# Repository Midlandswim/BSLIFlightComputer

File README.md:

BSLI Vanilla Board 

DevBoard for BSLI Liquid Rocket Systems Flight Computer

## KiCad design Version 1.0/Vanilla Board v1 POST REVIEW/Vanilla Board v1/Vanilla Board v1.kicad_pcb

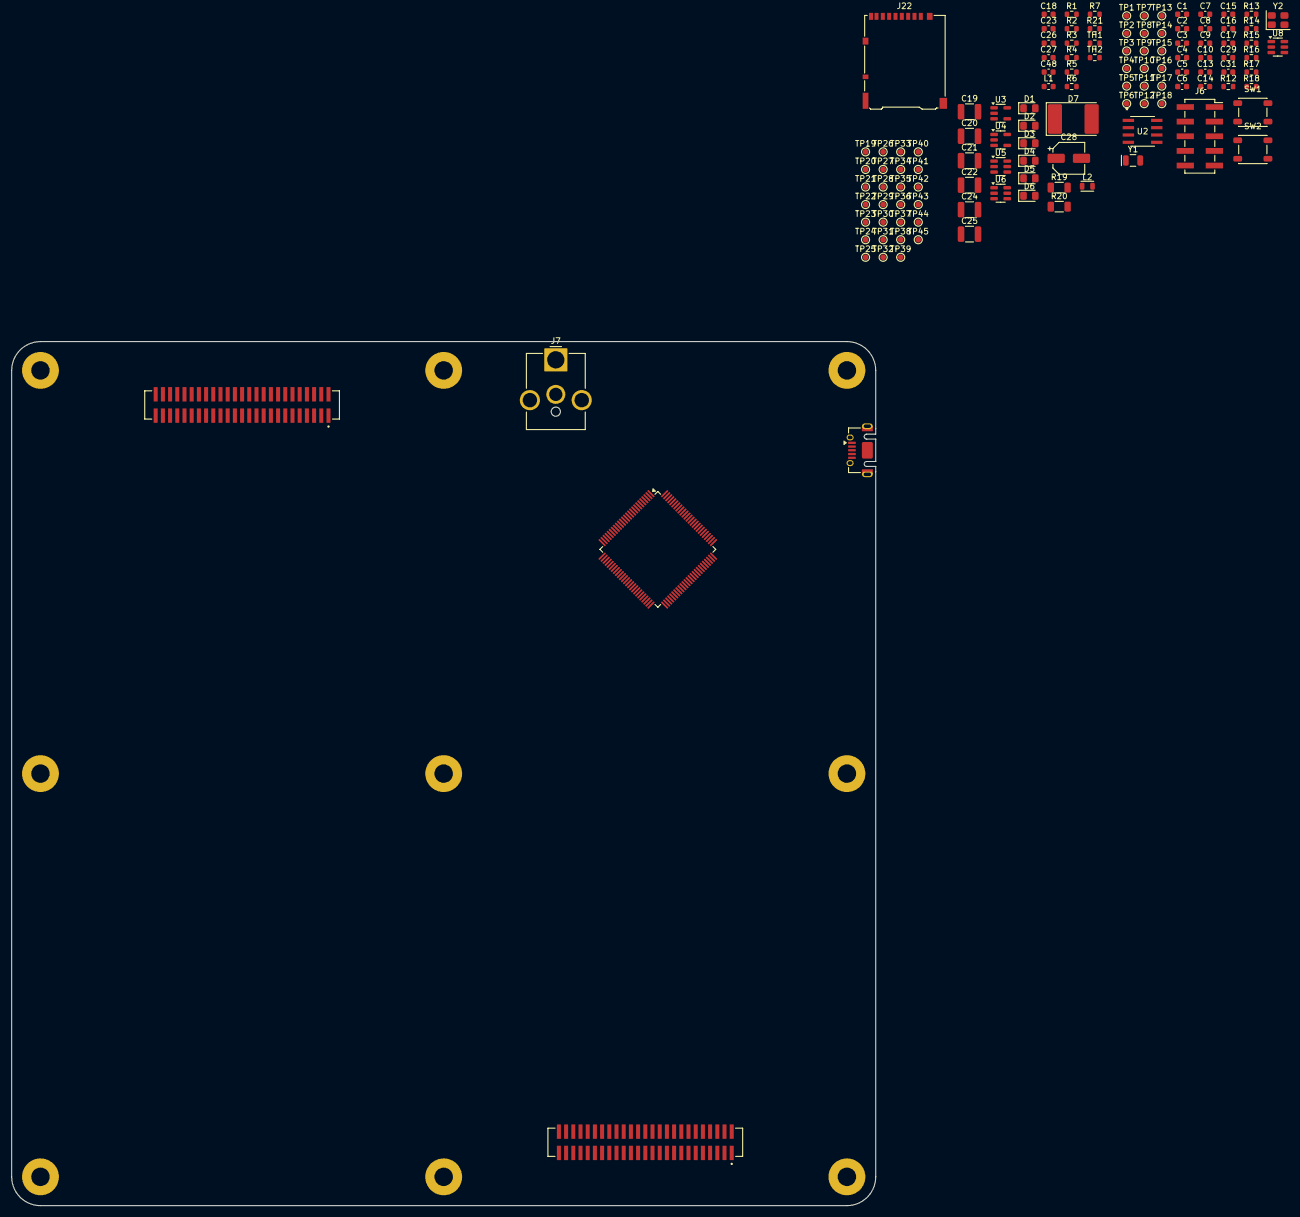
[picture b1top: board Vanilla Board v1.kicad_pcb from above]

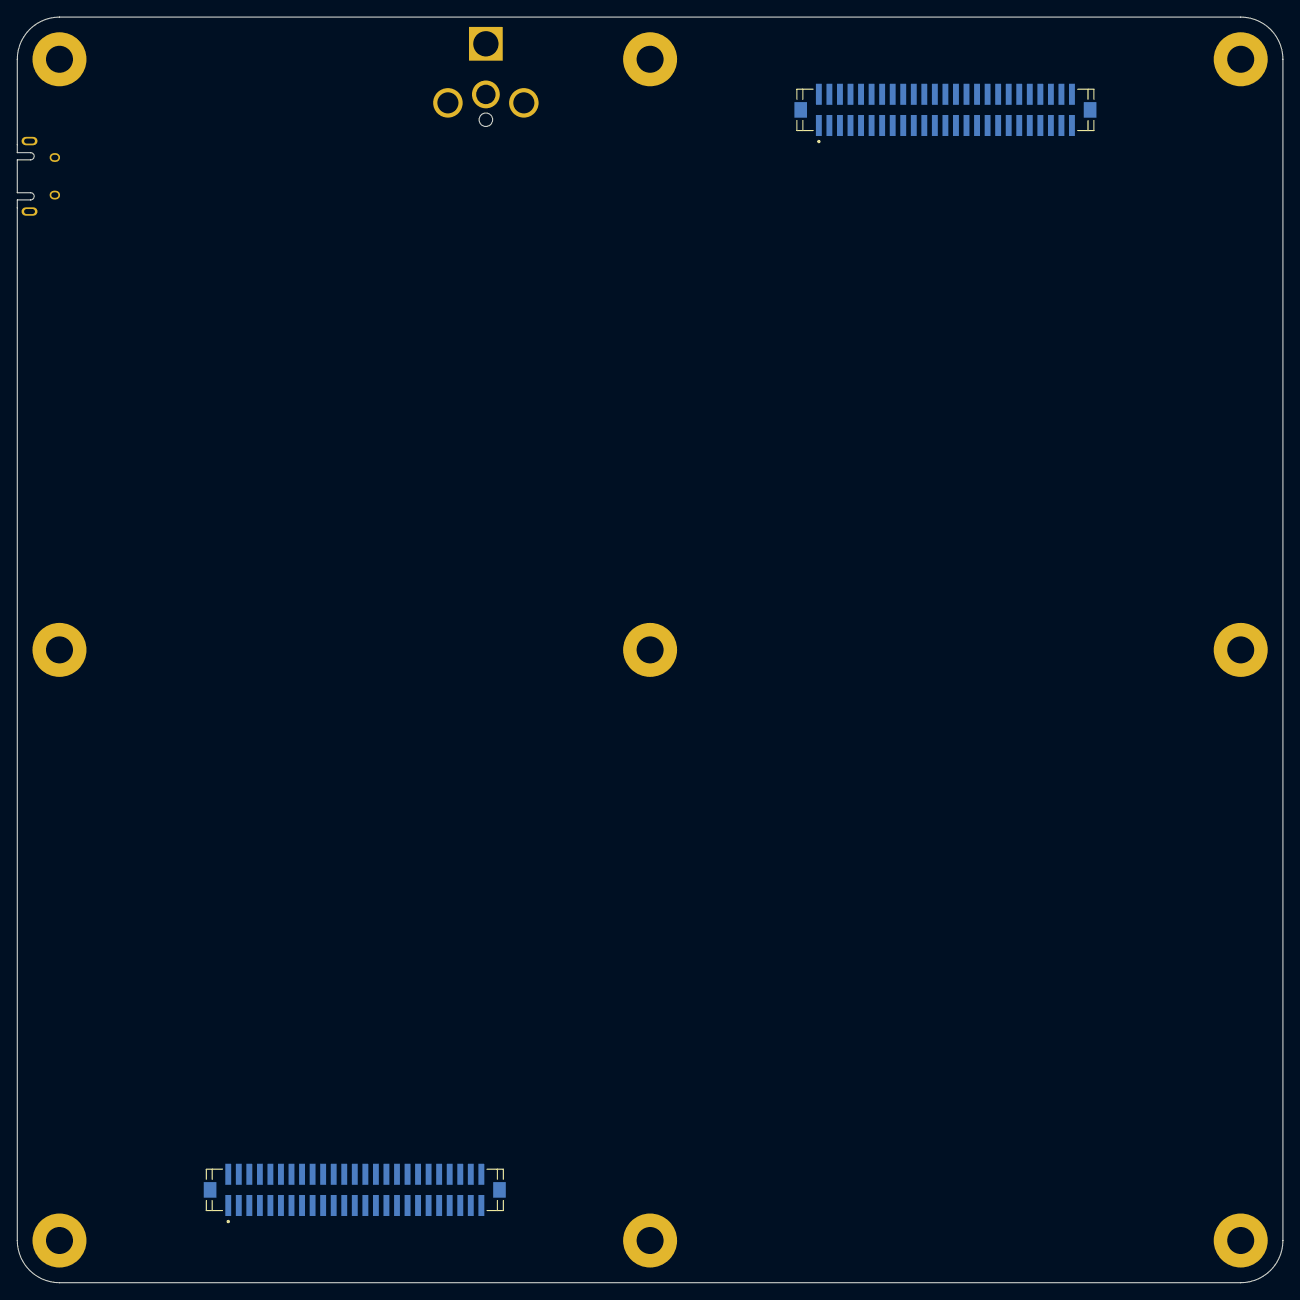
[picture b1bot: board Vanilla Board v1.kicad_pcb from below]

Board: 6 copper layers, 150.0 x 150.0 mm, 130 parts (2 on the bottom side), 139 nets, no tracks yet.

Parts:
C1, C2, C3, C4, C5, C6, C7, C16, C17, C18, C23, C26, C27: 100n; C_0603_1608Metric
C8: 100nF; C_0603_1608Metric
C9, C10, C14, C15: C_Small; C_0603_1608Metric
C13: 1u; C_0603_1608Metric
C19, C20, C21, C22: 22u; C_1210_3225Metric
C24, C25: 10u; C_1210_3225Metric
C28: 10uF; CP_Elec_5x5.9
C29: 4.7u; C_0603_1608Metric
C31: 10u; C_0603_1608Metric
C48: 10uF; C_0603_1608Metric
D1: BLU_LED; LED_0805_2012Metric_Pad1.15x1.40mm_HandSolder
D2: RED_LED; LED_0805_2012Metric_Pad1.15x1.40mm_HandSolder
D3: YLW_LED; LED_0805_2012Metric_Pad1.15x1.40mm_HandSolder
D4: GRN_LED; LED_0805_2012Metric_Pad1.15x1.40mm_HandSolder
D5: AMBR_LED; LED_0805_2012Metric_Pad1.15x1.40mm_HandSolder
D6: VILT_LED; LED_0805_2012Metric_Pad1.15x1.40mm_HandSolder
D7: D_Schottky; D_3220_8050Metric
H1, H2, H3, H4, H5, H6, H7, H8, H9: MountingHole_Pad; MountingHole_3.2mm_M3_Pad
J1: USB_OTG; USB_Micro-AB_Molex_47590-0001
J2, J4: G125-MS15005L3R; HARWIN_G125-MS15005L3R
J3, J5: G125-FS15005L0R; HARWIN_G125-FS15005L0R
J6: Conn_02x05_Counter_Clockwise; PinSocket_2x05_P2.54mm_Vertical_SMD
J7: Barrel_Jack; BarrelJack_CUI_PJ-063AH_Horizontal_CircularHoles
J22: Micro_SD_Card; microSD_HC_Hirose_DM3AT-SF-PEJM5
L1: 3.9u; L_0603_1608Metric
L2: 4.7u; L_TDK_MLZ2012_h1.25mm
R1, R2, R3, R4, R5, R21: 680; R_0603_1608Metric
R6: 22k; R_0603_1608Metric
R7: 100k; R_0603_1608Metric
R12: 4.7k; R_0603_1608Metric
R13, R16: 10k; R_0603_1608Metric
R14, R15: R_Small_US; R_0603_1608Metric
R17, R18: 60; R_0603_1608Metric
R19, R20: 1m; R_1206_3216Metric
SW1, SW2: SW_Push; SW_SPST_PTS647_Sx38
TH1, TH2: Thermistor_PTC; R_0603_1608Metric
TP1, TP2, TP3, TP4, TP5, TP6, TP7, TP8, TP9, TP10, TP11, TP12, TP13, TP14, TP15, TP16, TP17, TP18, TP19, TP20, TP21, TP22, TP23, TP24, TP25, TP26, TP27, TP28, TP29, TP30, TP31, TP32, TP33, TP34, TP35, TP36, TP37, TP38, TP39, TP40, TP41, TP42, TP43, TP44, TP45: TestPoint; TestPoint_Pad_D1.0mm
U1: STM32U575VITx; LQFP-100_14x14mm_P0.5mm
U2: ATA6561-GAQW-N; SOIC8_4P9X3P9MC_MCH
U3, U4: INA180A4; SOT-23-5
U5: AP63203WU; TSOT-23-6
U6: AP63205WU; TSOT-23-6
U8: USBLC6-2SC6; SOT-23-6
Y1: 32.768 kHz; Crystal_SMD_MicroCrystal_CC7V-T1A-2Pin_3.2x1.5mm
Y2: 16 MHz; Crystal_SMD_SeikoEpson_TSX3225-4Pin_3.2x2.5mm

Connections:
+3.3V: C1.1, C2.1, C3.1, C4.1, C5.1, C6.1, C13.1, C31.1, C48.1, J6.1, J22.4 (VDD), R1.1, R6.1, R19.2, SW2.2, TP16.1, TP26.1, TP37.1, U1.11 (VDD), U1.28 (VDD), U1.50 (VDD), U1.73 (VDDUSB), U1.75 (VDD), U1.100 (VDD), U2.5 (VIO), U4.4 (-)
+5V: C26.2, C27.2, R20.1, TP18.1, TP36.1, TP38.1, TP39.1, U2.3 (VCC), U3.4 (-), U3.5 (V+), U4.5 (V+)
/Mezzanine Connectors/Mez5: J2.5, J3.5
/Mezzanine Connectors/Mez6: J2.6, J3.6
/Mezzanine Connectors/Mez7: J2.7, J3.7
/Mezzanine Connectors/Mez8: J2.8, J3.8
/Mezzanine Connectors/Mez9: J2.9, J3.9
/Mezzanine Connectors/Mez10: J2.10, J3.10
/Mezzanine Connectors/Mez11: J2.11, J3.11
/Mezzanine Connectors/Mez12: J2.12, J3.12
/Mezzanine Connectors/Mez13: J2.13, J3.13
/Mezzanine Connectors/Mez14: J2.14, J3.14
/Mezzanine Connectors/Mez15: J2.15, J3.15
/Mezzanine Connectors/Mez16: J2.16, J3.16
/Mezzanine Connectors/Mez17: J2.17, J3.17
/Mezzanine Connectors/Mez18: J2.18, J3.18
/Mezzanine Connectors/Mez19: J2.19, J3.19
/Mezzanine Connectors/Mez20: J2.20, J3.20
/Mezzanine Connectors/Mez21: J2.21, J3.21
/Mezzanine Connectors/Mez22: J2.22, J3.22
/Mezzanine Connectors/Mez23: J2.23, J3.23
/Mezzanine Connectors/Mez24: J2.24, J3.24
/Mezzanine Connectors/Mez27: J2.49, J3.49
/Mezzanine Connectors/Mez28: J2.48, J3.48
/Mezzanine Connectors/Mez29: J2.47, J3.47
/Mezzanine Connectors/Mez30: J2.46, J3.46
/Mezzanine Connectors/Mez31: J2.45, J3.45
/Mezzanine Connectors/Mez32: J2.44, J3.44
/Mezzanine Connectors/Mez33: J2.43, J3.43
/Mezzanine Connectors/Mez34: J2.42, J3.42
/Mezzanine Connectors/Mez35: J2.41, J3.41
/Mezzanine Connectors/Mez36: J2.40, J3.40
/Mezzanine Connectors/Mez37: J2.39, J3.39
/Mezzanine Connectors/Mez38: J2.38, J3.38
/Mezzanine Connectors/Mez39: J2.37, J3.37
/Mezzanine Connectors/Mez40: J2.36, J3.36
/Mezzanine Connectors/Mez41: J2.35, J3.35
/Mezzanine Connectors/Mez42: J2.34, J3.34
/Mezzanine Connectors/Mez43: J2.33, J3.33
/Mezzanine Connectors/Mez44: J2.32, J3.32
/Mezzanine Connectors/Mez45: J2.31, J3.31
/Mezzanine Connectors/Mez46: J2.30, J3.30
/Mezzanine Connectors/Mez54: J4.4, J5.4
/Mezzanine Connectors/Mez55: J4.5, J5.5
/Mezzanine Connectors/Mez56: J4.6, J5.6
/Mezzanine Connectors/Mez57: J4.7, J5.7
/Mezzanine Connectors/Mez58: J4.8, J5.8
/Mezzanine Connectors/Mez59: J4.9, J5.9
/Mezzanine Connectors/Mez60: J4.10, J5.10
/Mezzanine Connectors/Mez61: J4.11, J5.11
/Mezzanine Connectors/Mez62: J4.12, J5.12
/Mezzanine Connectors/Mez63: J4.13, J5.13
/Mezzanine Connectors/Mez64: J4.14, J5.14
/Mezzanine Connectors/Mez65: J4.15, J5.15
/Mezzanine Connectors/Mez66: J4.16, J5.16
/Mezzanine Connectors/Mez67: J4.17, J5.17
/Mezzanine Connectors/Mez68: J4.18, J5.18
/Mezzanine Connectors/Mez69: J4.19, J5.19
/Mezzanine Connectors/Mez70: J4.20, J5.20
/Mezzanine Connectors/Mez71: J4.21, J5.21
/Mezzanine Connectors/Mez72: J4.22, J5.22
/Mezzanine Connectors/Mez79: J4.47, J5.47
/Mezzanine Connectors/Mez80: J4.46, J5.46
/Mezzanine Connectors/Mez81: J4.45, J5.45
/Mezzanine Connectors/Mez82: J4.44, J5.44
/Mezzanine Connectors/Mez83: J4.43, J5.43
/Mezzanine Connectors/Mez84: J4.42, J5.42
/Mezzanine Connectors/Mez85: J4.41, J5.41
/Mezzanine Connectors/Mez86: J4.40, J5.40
/Mezzanine Connectors/Mez87: J4.39, J5.39
/Mezzanine Connectors/Mez88: J4.38, J5.38
/Mezzanine Connectors/Mez89: J4.37, J5.37
/Mezzanine Connectors/Mez90: J4.36, J5.36
/Mezzanine Connectors/Mez91: J4.35, J5.35
/Mezzanine Connectors/Mez92: J4.34, J5.34
/Mezzanine Connectors/Mez93: J4.33, J5.33
/Mezzanine Connectors/Mez94: J4.32, J5.32
/Mezzanine Connectors/Mez95: J4.31, J5.31
/Mezzanine Connectors/Mez96: J4.30, J5.30
/Mezzanine Connectors/Mez97: J4.29, J5.29
CAN+: J4.24, J5.24, R17.1, TP7.1, U2.7 (CANH)
CAN-: J4.49, J5.49, R18.2, TP8.1, U2.6 (CANL)
CANTRX_STBY: U1.90 (PB4), U2.8 (STBY)
FLTCLK_N: J4.27, J5.27
FLTCLK_P: J4.2, J5.2
GND: C1.2, C2.2, C3.2, C4.2, C5.2, C6.2, C7.2, C8.1, C9.2, C10.2, C13.2, C14.2, C15.2, C16.2, C17.2, C19.2, C20.2, C21.2, C22.2, C24.2, C25.2, C26.1, C27.1, C28.2, C29.2, C31.2, C48.2, D1.1 (K), D2.1 (K), D3.1 (K), D4.1 (K), D5.1 (K), D6.1 (K), H1.1, H2.1, H3.1, H4.1, H5.1, H6.1, H7.1, H8.1, H9.1, J1.5 (GND), J1.6 (Shield), J2.1, J2.4, J2.25, J2.26, J2.29, J2.50, J3.1, J3.4, J3.25, J3.26, J3.29, J3.50, J4.1, J4.3, J4.23, J4.25, J4.26, J4.28, J4.48, J4.50, J5.1, J5.3, J5.23, J5.25, J5.26, J5.28, J5.48, J5.50, J6.2, J6.3, J6.5, J7.2, J22.6 (VSS), J22.9 (SHIELD), R7.2, R13.2, R16.2, SW1.2, TP17.1, TP28.1, TP40.1, TP41.1, U1.10 (VSS), U1.19 (VSSA), U1.27 (VSS), U1.49 (VSS), U1.74 (VSS), U1.99 (VSS), U2.2 (GND), U3.2 (GND), U4.2 (GND), U5.4 (GND), U6.4 (GND), U8.2 (GND)
I_3.3: TP43.1, U1.63 (PC6), U4.1
I_5: TP42.1, U1.34 (PC5), U3.1
MICRO_USB_D+: J1.3 (D+), U8.6 (I/O1)
MICRO_USB_D-: J1.2 (D-), U8.4 (I/O2)
NRST/RESET: C8.2, J6.6, SW1.1, TP3.1, U1.14 (NRST)
unnamed: C10.1, R15.2, TP5.1, Y1.2
unnamed: C14.1, R14.2, TP9.1, Y2.2
unnamed: C17.1, R17.2, R18.1
unnamed: D1.2 (A), R1.2
unnamed: D2.2 (A), R2.2
unnamed: D3.2 (A), R3.2
unnamed: D4.2 (A), R4.2
unnamed: D5.2 (A), R5.2
unnamed: D6.2 (A), R21.2
unnamed: D7.2 (A), J7.1, TP19.1
unnamed: C29.1, U1.48 (VCAP)
unnamed: C19.1, C20.1, L2.2, R20.2, TP35.1, U3.3 (+), U6.1 (FB)
unnamed: C21.1, C22.1, L1.2, R19.1, TP34.1, U4.3 (+), U5.1 (FB)
unnamed: C23.1, U5.6 (BST)
unnamed: C25.1, TH1.1, TP31.1, U5.2 (EN), U5.3 (IN)
unnamed: C23.2, L1.1, TP32.1, U5.5 (SW)
unnamed: C18.1, U6.6 (BST)
unnamed: C24.1, TH2.1, TP30.1, U6.2 (EN), U6.3 (IN)
unnamed: C18.2, L2.1, TP33.1, U6.5 (SW)
PA9/USB_OTG_FS_VBUS: R12.2, R13.1, TP11.1, U1.68 (PA9)
PA10/USB_OTG_FS_ID: J1.4 (ID), TP2.1, U1.69 (PA10)
PA13/SWDIO: J6.10, U1.72 (PA13)
PA14/SWCLK: J6.9, U1.76 (PA14)
PC0/ADC4_1: R6.2, R7.1, U1.15 (PC0)
PC14/LSE_IN: R15.1, U1.8 (PC14)
PC15/LSE_OUT: C9.1, TP6.1, U1.9 (PC15), Y1.1
PD0/FDCAN1_RX: TP13.1, U1.81 (PD0), U2.4 (RXD)
PD1/FDCAN1_TX: TP12.1, U1.82 (PD1), U2.1 (TXD)
PH0/HSE_IN: R14.1, U1.12 (PH0)
PH1/HSE_OUT: C15.1, TP10.1, U1.13 (PH1), Y2.1
PH3/BOOT0: C16.1, R16.1, SW2.1, TP4.1, U1.94 (PH3)
RGB_LED_BLU: TP23.1, U1.44 (PE13)
RGB_LED_GRN: TP22.1, U1.43 (PE12)
RGB_LED_RED: TP21.1, U1.42 (PE11)
SD_CS: J22.2 (DAT3/CD), TP25.1, U1.16 (PC1)
SD_SPI2_MISO: J22.7 (DAT0), TP27.1, U1.17 (PC2)
SD_SPI2_MOSI: J22.3 (CMD), TP24.1, U1.18 (PC3)
SD_SPI2_SCK: J22.5 (CLK), TP29.1, U1.47 (PB10)
STATUS_LED_1: R2.1, U1.35 (PB0)
STATUS_LED_2: R3.1, U1.36 (PB1)
STATUS_LED_3: R4.1, U1.37 (PB2)
STATUS_LED_4: R5.1, U1.89 (PB3)
STATUS_LED_5: R21.1, U1.91 (PB5)
USB_5V: J1.1 (VBUS), R12.1, TP1.1, U8.5 (VBUS)
USB_D+: TP15.1, U1.71 (PA12), U8.1 (I/O1)
USB_D-: TP14.1, U1.70 (PA11), U8.3 (I/O2)
VBUS: C28.1, D7.1 (K), J2.2, J2.3, J2.27, J2.28, J3.2, J3.3, J3.27, J3.28, TH1.2, TH2.2, TP20.1, TP44.1, TP45.1
VDDA: C7.1, U1.22 (VDDA)

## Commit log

2025-09-21 Version1
    Attempt at posting version 1.0 post review board files
